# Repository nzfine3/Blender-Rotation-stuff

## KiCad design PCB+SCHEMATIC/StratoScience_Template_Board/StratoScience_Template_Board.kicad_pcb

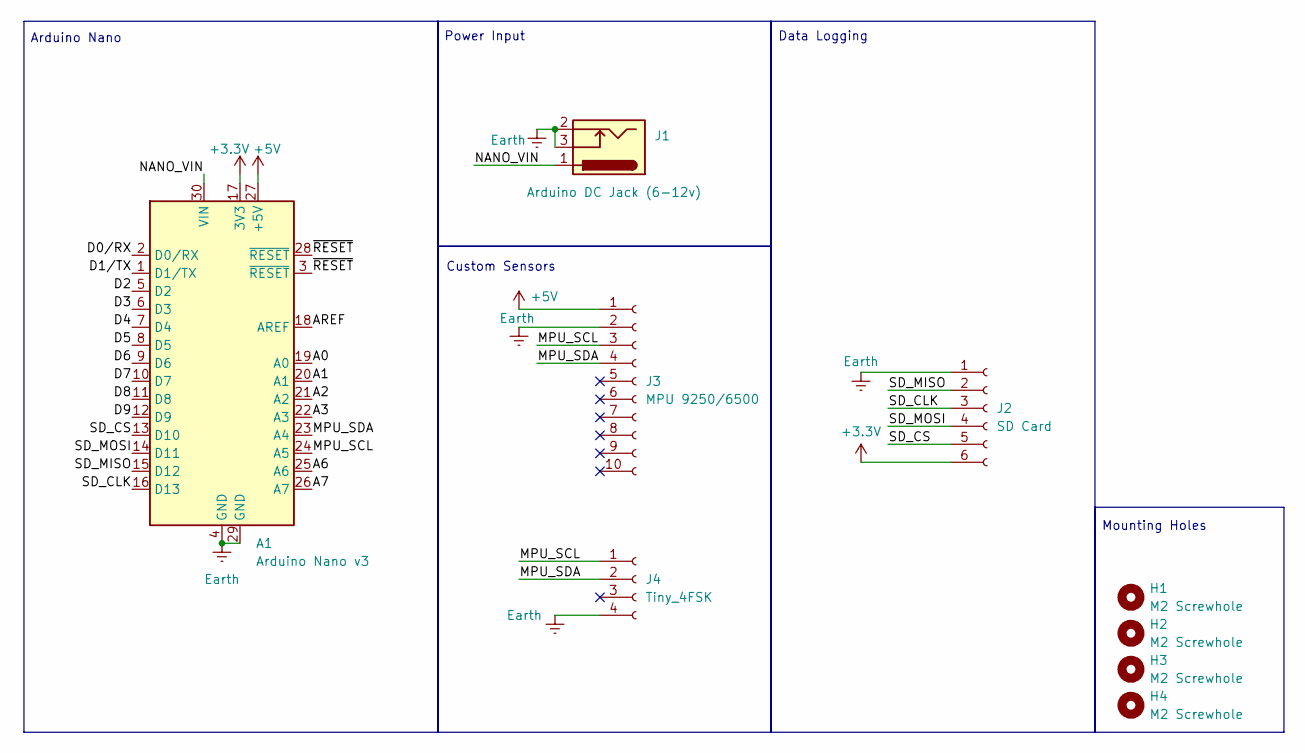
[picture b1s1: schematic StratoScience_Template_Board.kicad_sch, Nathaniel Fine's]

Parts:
A1: Arduino Nano v3; Arduino_Nano
H1, H2, H3, H4: M2 Screwhole; MountingHole_2.2mm_M2
J1: Arduino DC Jack (6-12v); BarrelJack_GCT_DCJ200-10-A_Horizontal
J2: SD Card; PinSocket_1x06_P2.54mm_Vertical
J3: MPU 9250/6500; PinSocket_1x10_P2.54mm_Vertical
J4: Tiny_4FSK; JST_PH_B4B-PH-K_1x04_P2.00mm_Vertical

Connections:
+3.3V: A1.17 (3V3), J2.6
+5V: A1.27 (+5V), J3.1
/A0: A1.19 (A0)
/A1: A1.20 (A1)
/A2: A1.21 (A2)
/A3: A1.22 (A3)
/A6: A1.25 (A6)
/A7: A1.26 (A7)
/AREF: A1.18 (AREF)
/D0/RX: A1.2 (D0/RX)
/D1/TX: A1.1 (D1/TX)
/D2: A1.5 (D2)
/D3: A1.6 (D3)
/D4: A1.7 (D4)
/D5: A1.8 (D5)
/D6: A1.9 (D6)
/D7: A1.10 (D7)
/D8: A1.11 (D8)
/D9: A1.12 (D9)
/MPU_SCL: A1.24 (A5), J3.3, J4.1
/MPU_SDA: A1.23 (A4), J3.4, J4.2
/NANO_VIN: A1.30 (VIN), J1.1
/SD_CLK: A1.16 (D13), J2.3
/SD_CS: A1.13 (D10), J2.5
/SD_MISO: A1.15 (D12), J2.2
/SD_MOSI: A1.14 (D11), J2.4
/~RESET: A1.3 (~RESET), A1.28 (~RESET)
Earth: A1.4 (GND), A1.29 (GND), J1.2, J1.3, J2.1, J3.2, J4.4

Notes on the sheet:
Data Logging
Custom Sensors
Power Input
Arduino Nano
Mounting Holes

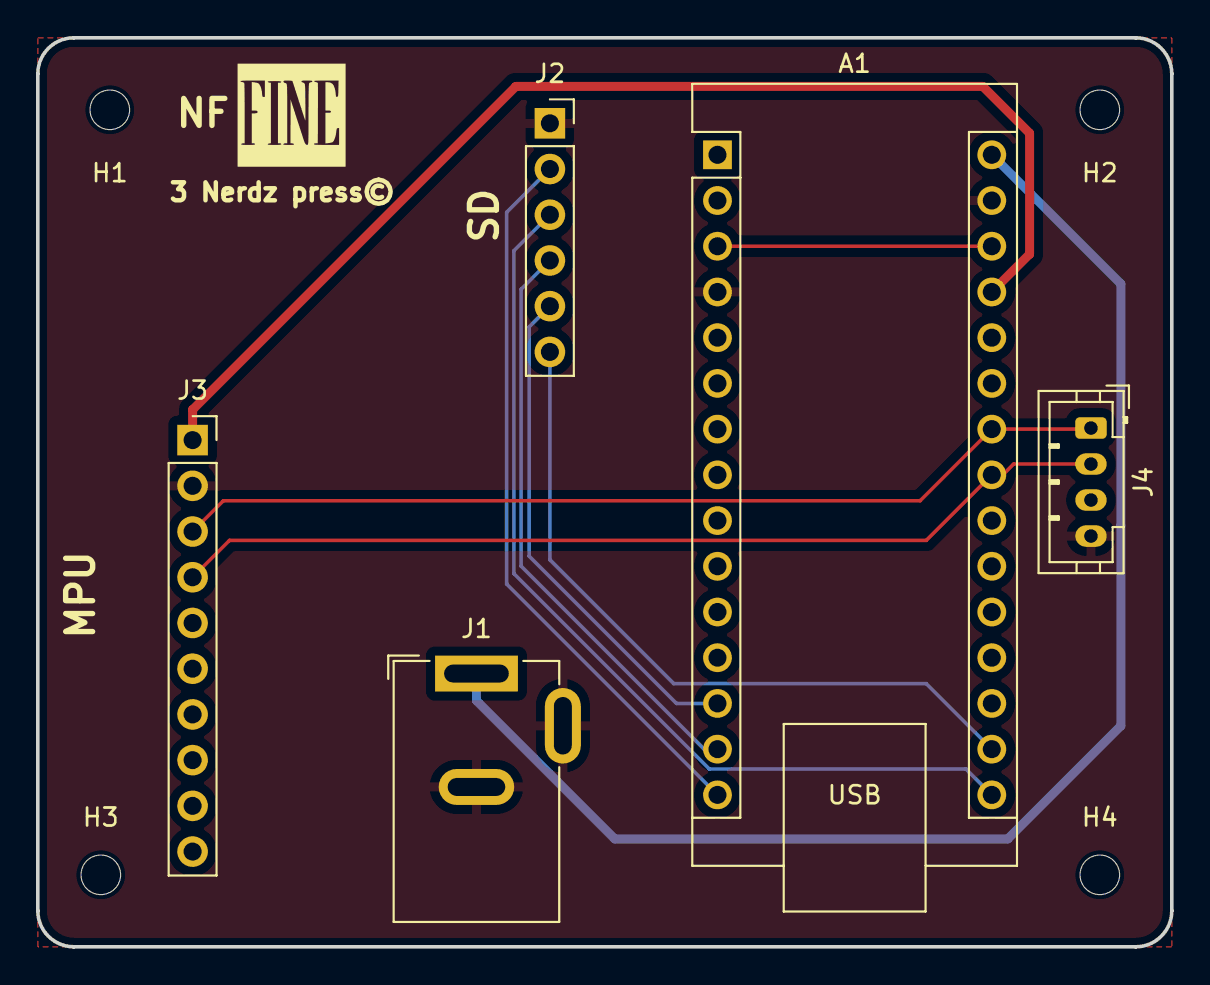
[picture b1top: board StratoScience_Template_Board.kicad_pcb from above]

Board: 2 copper layers, 63.0 x 50.5 mm, 9 parts (0 on the bottom side), 11 nets.

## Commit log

2025-03-03 Adding working code
    Adding the working code and fixing bugs
2025-03-04 adding more sample values, lowering update time for more efficiency
2025-03-04 added more in-depth comments
2025-03-09 adding SD card compatability and fixed some bugs by rewriting code
2025-03-09 adding compatibility for connection to sondehub
2025-03-11 adding more sondehub combatibility
2025-03-11 selection code added
2025-03-14 Added Final_Folder, also added 3d compatability
2025-03-15 fixed bugs and now the arduino code works. Also made the balloon model in localhoast better
2025-03-22 Adding RX and TX compatability.
    I added RX - D4, TX - D5 to connect with Tiny4.
2025-03-22 Fixing bugs, removing serial and adding I2C. Adding test file also.
2025-04-05 Fixed bugs: I2C compatability
2025-04-12 Adding arduino / vscode compatability and adding requestEvent
2025-05-03 Adding PCB stuff
    Adding stuff for PCB
2025-05-10 adding stuff
    just adding stuff
2025-06-07 Update serial number and optimize I2C data transmission in Arduino code
2025-06-14 Fixing bugs and adding the ameteur prefix
2025-07-07 updating code
2025-07-08 adding softwire for more i2c pins, code shuttof on Tiny4FSK side
